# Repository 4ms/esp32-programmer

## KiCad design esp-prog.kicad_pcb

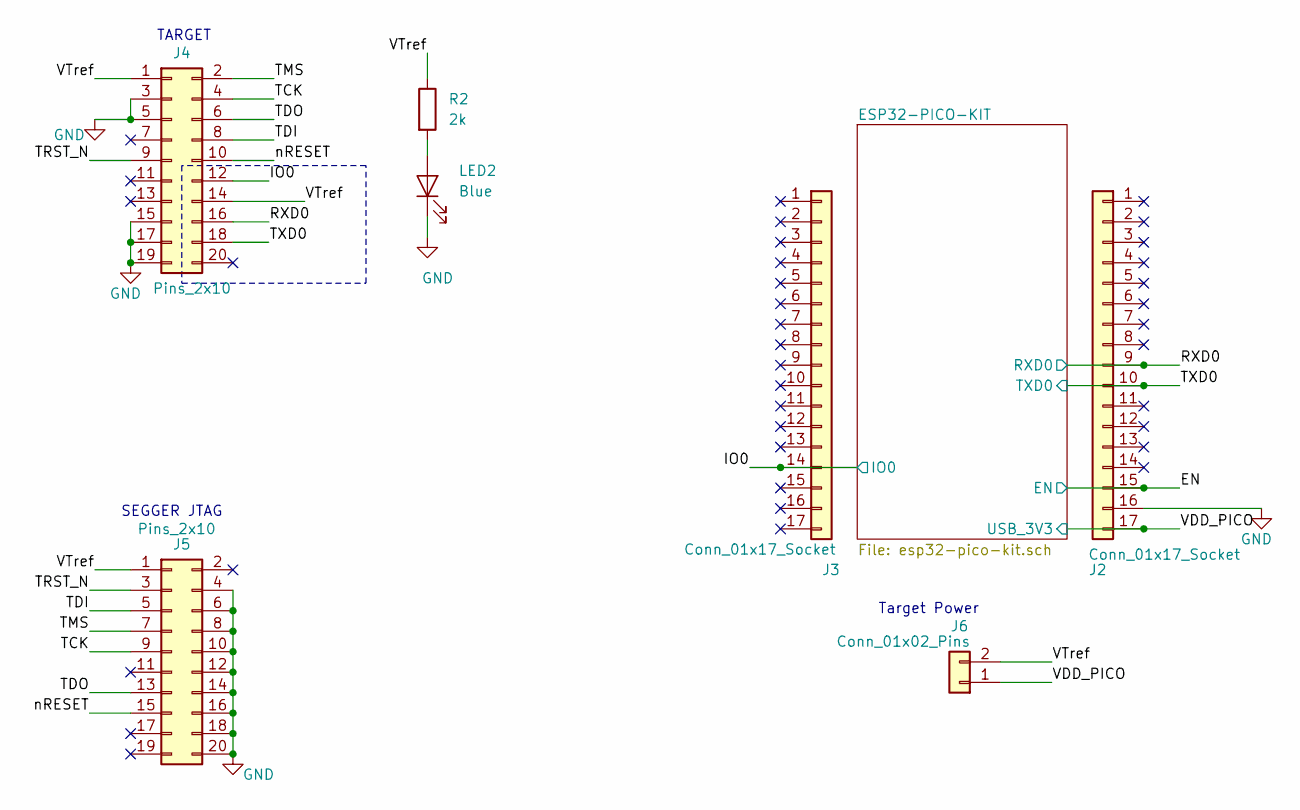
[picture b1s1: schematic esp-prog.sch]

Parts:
J2, J3: Conn_01x17_Socket; PinSocket_1x17_P2.54mm_Vertical
J4: Pins_2x10; Pins_2x10_1.27mm_SMT_Trace
J5: Pins_2x10; PinHeader_2x10_P2.54mm_Vertical
J6: Conn_01x02_Pins; Pins_1x02_2.54mm_TH
LED2: Blue; LED_0603_1608Metric
R2: 2k; R_0603

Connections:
/EN: J2.15; also elsewhere on the board
/IO0: J3.14, J4.12; also elsewhere on the board
/RXD0: J2.9, J4.16; also elsewhere on the board
/TCK: J4.4, J5.9
/TDI: J4.8, J5.5
/TDO: J4.6, J5.13
/TMS: J4.2, J5.7
/TRST_N: J4.9, J5.3
/TXD0: J2.10, J4.18; also elsewhere on the board
/VDD_PICO: J2.17, J6.1; also elsewhere on the board
/VTref: J4.1, J4.14, J5.1, J6.2, R2.1
/nRESET: J4.10, J5.15
GND: J2.16, J4.3, J4.5, J4.15, J4.17, J4.19, J5.4, J5.6, J5.8, J5.10, J5.12, J5.14, J5.16, J5.18, J5.20, LED2.1 (K); also elsewhere on the board
unnamed: LED2.2 (A), R2.2

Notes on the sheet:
Target Power
SEGGER JTAG
TARGET

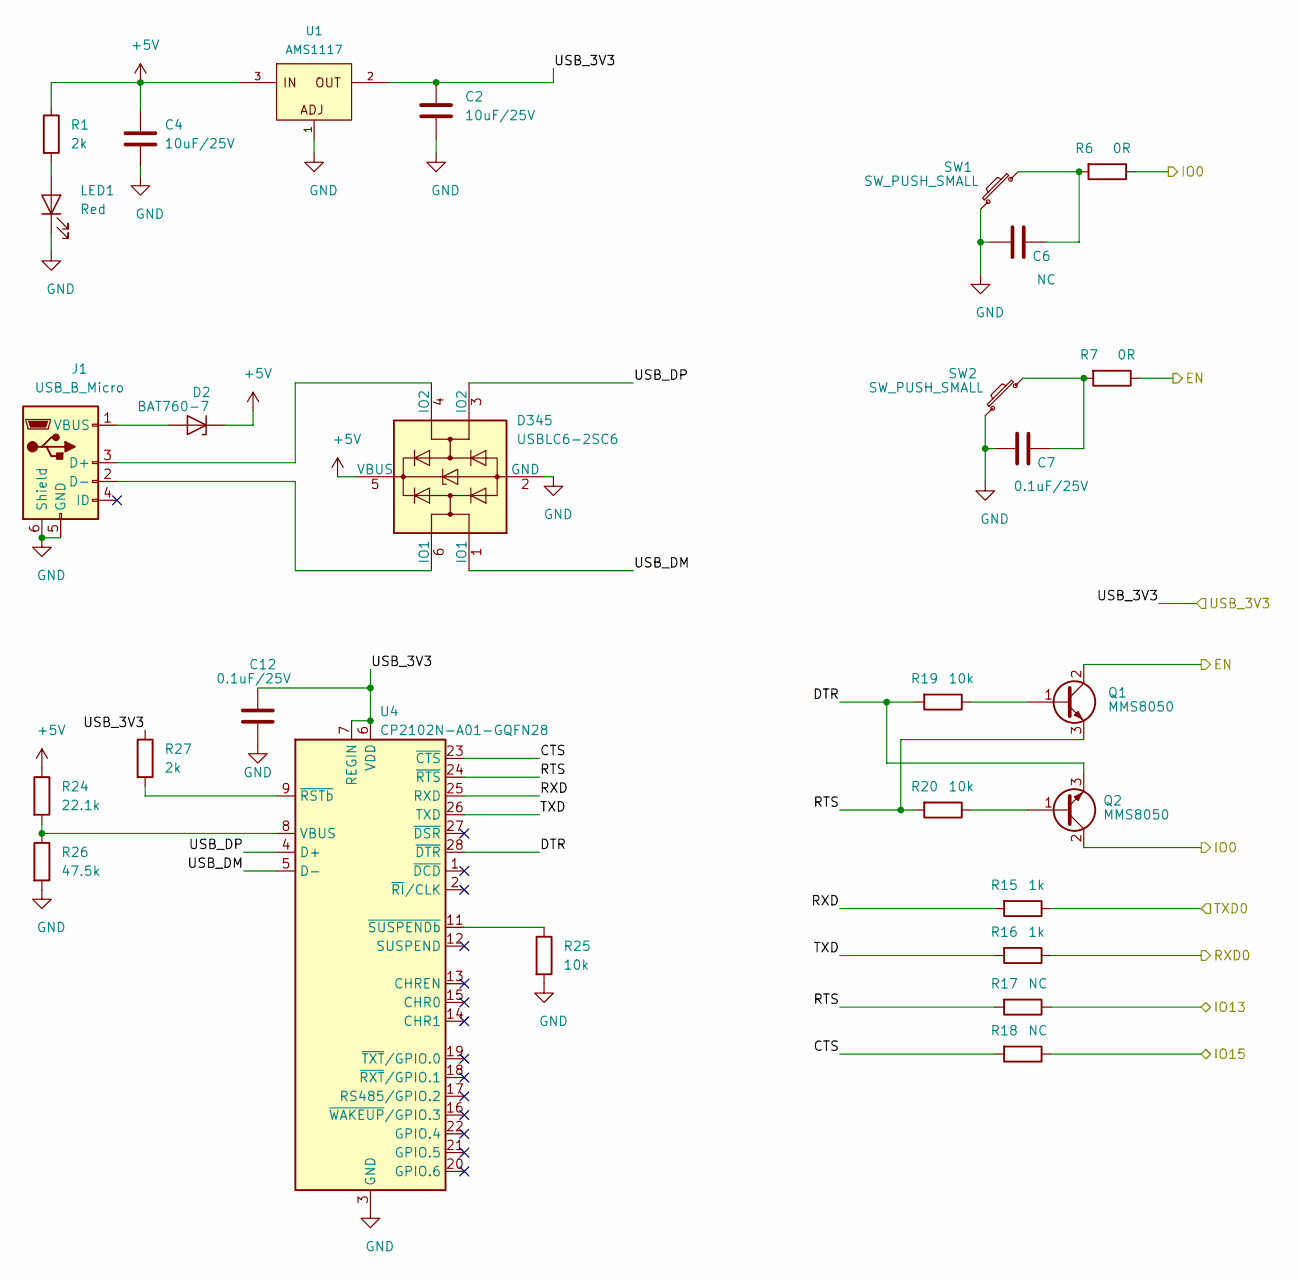
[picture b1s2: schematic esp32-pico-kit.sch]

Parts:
C2, C4: 10uF/25V; C_0603
C6: NC; C_0603
C7, C12: 0.1uF/25V; C_0603
D2: BAT760-7; D_SOD-323F
D345: USBLC6-2SC6; SOT-23-6
J1: USB_B_Micro; USB_Micro-B_Molex-105017-0001
LED1: Red; LED_0603_1608Metric
Q1, Q2: MMS8050; SOT23-3_PO123
R1, R27: 2k; R_0603
R6, R7: 0R; R_0603
R15, R16: 1k; R_0603
R17, R18: NC; R_0603
R19, R20, R25: 10k; R_0603
R24: 22.1k; R_0603
R26: 47.5k; R_0603
SW1, SW2: SW_PUSH_SMALL; Button_Tact_PTS540
U1: AMS1117; SOT223
U4: CP2102N-A01-GQFN28; QFN-28-1EP_5x5mm_P0.5mm_EP3.35x3.35mm

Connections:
+5V: C4.1, D2.1 (K), D345.5 (VBUS), R1.1, R24.1, U1.3 (IN)
/EN: Q1.2 (C), R7.1; also elsewhere on the board
/ESP32-PICO-KIT/CTS: R18.2, U4.23 (~CTS)
/ESP32-PICO-KIT/DTR: Q2.3 (E), R19.2, U4.28 (~DTR)
/ESP32-PICO-KIT/IO13: R17.1
/ESP32-PICO-KIT/IO15: R18.1
/ESP32-PICO-KIT/RTS: Q1.3 (E), R17.2, R20.2, U4.24 (~RTS)
/ESP32-PICO-KIT/RXD: R15.2, U4.25 (RXD)
/ESP32-PICO-KIT/TXD: R16.2, U4.26 (TXD)
/ESP32-PICO-KIT/USB_DM: D345.1 (IO1), U4.5 (D-)
/ESP32-PICO-KIT/USB_DP: D345.3 (IO2), U4.4 (D+)
/IO0: Q2.2 (C), R6.1; also elsewhere on the board
/RXD0: R16.1; also elsewhere on the board
/TXD0: R15.1; also elsewhere on the board
/VDD_PICO: C2.1, C12.1, R27.1, U1.2 (OUT), U4.6 (VDD), U4.7 (REGIN); also elsewhere on the board
GND: C2.2, C4.2, C6.1, C7.1, C12.2, D345.2 (GND), J1.5 (GND), J1.6 (Shield), LED1.1 (K), R25.2, R26.2, SW1.1, SW2.1, U1.1 (ADJ), U4.3 (GND), U4.29 (GND); also elsewhere on the board
unnamed: C6.2, R6.2, SW1.2
unnamed: C7.2, R7.2, SW2.2
unnamed: D2.2 (A), J1.1 (VBUS)
unnamed: D345.4 (IO2), J1.3 (D+)
unnamed: D345.6 (IO1), J1.2 (D-)
unnamed: LED1.2 (A), R1.2
unnamed: Q1.1 (B), R19.1
unnamed: Q2.1 (B), R20.1
unnamed: R24.2, R26.1, U4.8 (VBUS)
unnamed: R25.1, U4.11 (~SUSPENDb)
unnamed: R27.2, U4.9 (~RSTb)

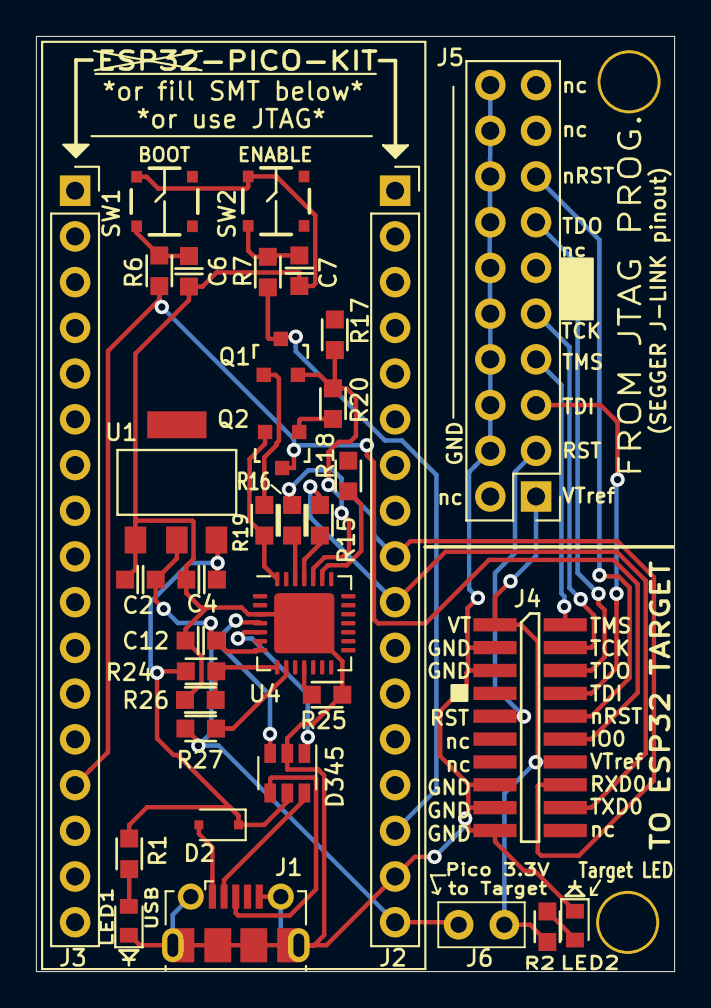
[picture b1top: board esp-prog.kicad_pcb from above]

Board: 2 copper layers, 35.5 x 51.9 mm, 37 parts (0 on the bottom side), 33 nets.

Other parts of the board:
M?: 561-###TAB; MountingHole_XXXTAB_AdhesiveBase
M?#2: 561-###TAB; MountingHole_XXXTAB_AdhesiveBase

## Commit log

2020-02-25 Initial commit: layout is WIP
2020-02-26 few more traces
2020-02-26 Finished layout
2020-02-28 Final cleanup of silk. Created gerbers (oshpark ordered)
